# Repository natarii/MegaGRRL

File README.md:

MegaGRRL - Real Hardware Sega Genesis VGM Player
========
**MegaGRRL** is an ESP32-powered VGM player, playing tracks from the Sega Mega Drive/Genesis, Master System, and more on real YM2612 and SN76489 sound chips.

## Overview
MegaGRRL is a system comprised of ESP32-powered hardware to interface with original YM2612 and SN76489 sound chips, and FreeRTOS-based firmware using the ESP-IDF framework. Its playback engine is focused on high accuracy and supporting as many features of the VGM file format as possible. It is a completely standalone player, requiring no connection to a host PC. MegaGRRL OS has a fully-featured, easy to use UI, and several unique features which make it the premier hardware playback solution.

There are currently two main hardware versions. The same firmware targets both.
  * **MegaGRRL Desktop**
  * **MegaGRRL Portable** (still in development)

The MegaGRRL Desktop hardware also supports the following **MegaMods** allowing sound chips other than the YM2612/SN76489 to be used:
  * **OPNA MegaMod** - Uses the OPNA (YM2608). Can also play VGMs for OPN (YM2203) and AY-3-8910.
  * **OPL3 MegaMod** - Uses the OPL3 (YMF262). Can also play VGMs for OPL2 (YM3812) and OPL (YM3526).

This repository contains the MegaGRRL OS firmware, and includes the hardware as submodules. Use `--recursive` when cloning the repo to get the hardware files as well.

  * **esp-idf-patches/** - ESP-IDF v3.3.4 SPI master driver patches, required for build
  * **hardware/** - Hardware files for all base board versions, and MegaMods for the Desktop version
  * **firmware/** - Firmware for the ESP32
  * **utils/** - Utilities, such as for packing firmware updates

## Compiling and initial flash
  * Windows users: A complete guide is available [here](https://git.agiri.ninja/snippets/3).
  * Other platforms: MegaGRRL OS is built like a standard ESP-IDF v3.3.4 project, but some patches are required. Please see [doc/compiling.md](https://git.agiri.ninja/natalie/megagrrl/-/blob/master/doc/compiling.md) for more information.

## Updating firmware
To update to the latest firmware after your player is up and running, download the latest .mgu file for your hardware version (desktop or portable) from the [Releases page](https://git.agiri.ninja/natalie/megagrrl/-/releases) and copy it to the SD card. Launch the update from MegaGRRL's file browser.

## Obtaining VGM files
The defacto standard Genesis/Mega Drive VGM repository is [Project 2612](https://project2612.org/). Both .vgm and .vgz files are supported, but load times are shorter if using vgm. VGMs for other sound chips can be obtained from [VGMRips](https://vgmrips.net/packs/).

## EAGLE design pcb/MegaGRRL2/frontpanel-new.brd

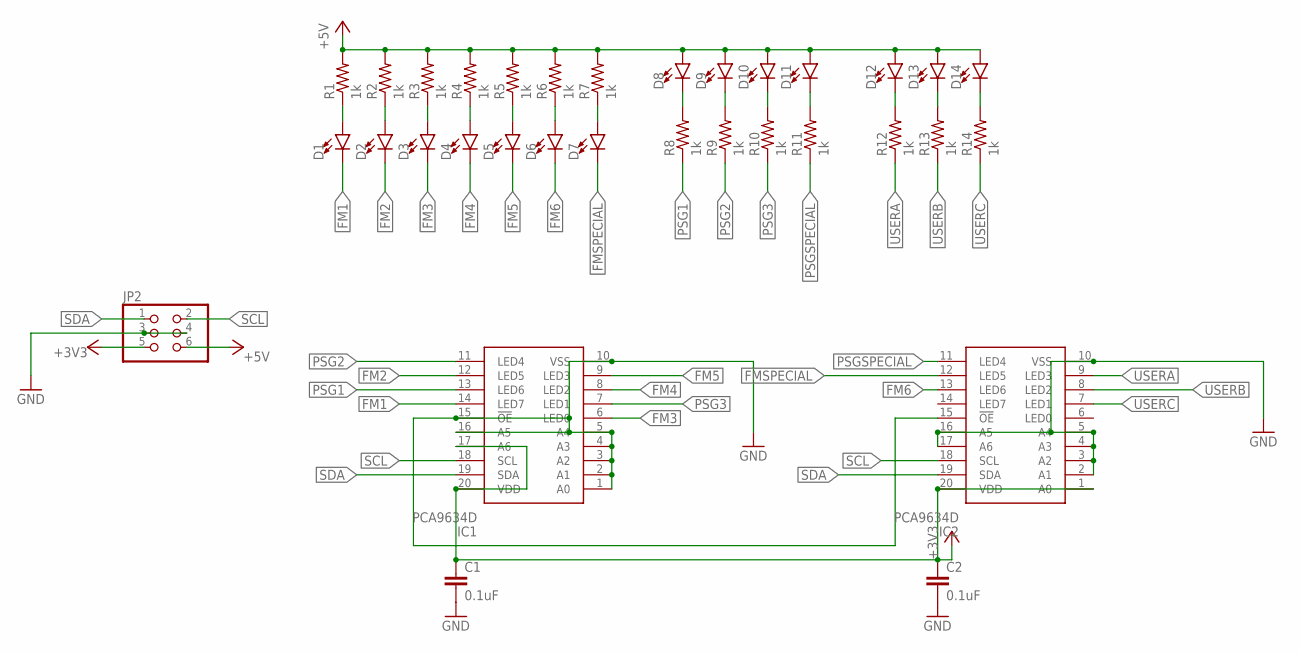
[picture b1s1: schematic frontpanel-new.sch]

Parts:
C1, C2: 0.1uF; C0805
D1, D2, D3, D4, D5, D6, D7, D8, D9, D10, D11, D12, D13, D14: AM2520; AM2520HOLE
IC1, IC2: PCA9634D; SOIC127P1032X265-20N
JP2: PINHD-2X3SMT; 2X03_SMT
R1, R2, R3, R4, R5, R6, R7, R8, R9, R10, R11, R12, R13, R14: 1k; R0805

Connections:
+3V3: C1.1, C2.1, IC1.17 (A6), IC1.20 (VDD), IC2.1 (A0), IC2.20 (VDD), JP2.5
+5V: D8.A, D9.A, D10.A, D11.A, D12.A, D13.A, D14.A, JP2.6, R1.2, R2.2, R3.2, R4.2, R5.2, R6.2, R7.2
FM1: D1.C, IC1.14 (LED7)
FM2: D2.C, IC1.12 (LED5)
FM3: D3.C, IC1.6 (LED0)
FM4: D4.C, IC1.8 (LED2)
FM5: D5.C, IC1.9 (LED3)
FM6: D6.C, IC2.13 (LED6)
FMSPECIAL: D7.C, IC2.12 (LED5)
GND: C1.2, C2.2, IC1.1 (A0), IC1.2 (A1), IC1.3 (A2), IC1.4 (A3), IC1.5 (A4), IC1.10 (VSS), IC1.15 (!OE), IC1.16 (A5), IC2.2 (A1), IC2.3 (A2), IC2.4 (A3), IC2.5 (A4), IC2.10 (VSS), IC2.15 (!OE), IC2.16 (A5), IC2.17 (A6), JP2.3, JP2.4
unnamed: D12.C, R12.2
unnamed: D1.A, R1.1
unnamed: D5.A, R5.1
unnamed: D3.A, R3.1
unnamed: D6.A, R6.1
unnamed: D4.A, R4.1
unnamed: D2.A, R2.1
unnamed: D7.A, R7.1
unnamed: D8.C, R8.2
unnamed: D9.C, R9.2
unnamed: D10.C, R10.2
unnamed: D11.C, R11.2
unnamed: D13.C, R13.2
unnamed: D14.C, R14.2
PSG1: IC1.13 (LED6), R8.1
PSG2: IC1.11 (LED4), R9.1
PSG3: IC1.7 (LED1), R10.1
PSGSPECIAL: IC2.11 (LED4), R11.1
SCL: IC1.18 (SCL), IC2.18 (SCL), JP2.2
SDA: IC1.19 (SDA), IC2.19 (SDA), JP2.1
USERA: IC2.9 (LED3), R12.1
USERB: IC2.8 (LED2), R13.1
USERC: IC2.7 (LED1), R14.1

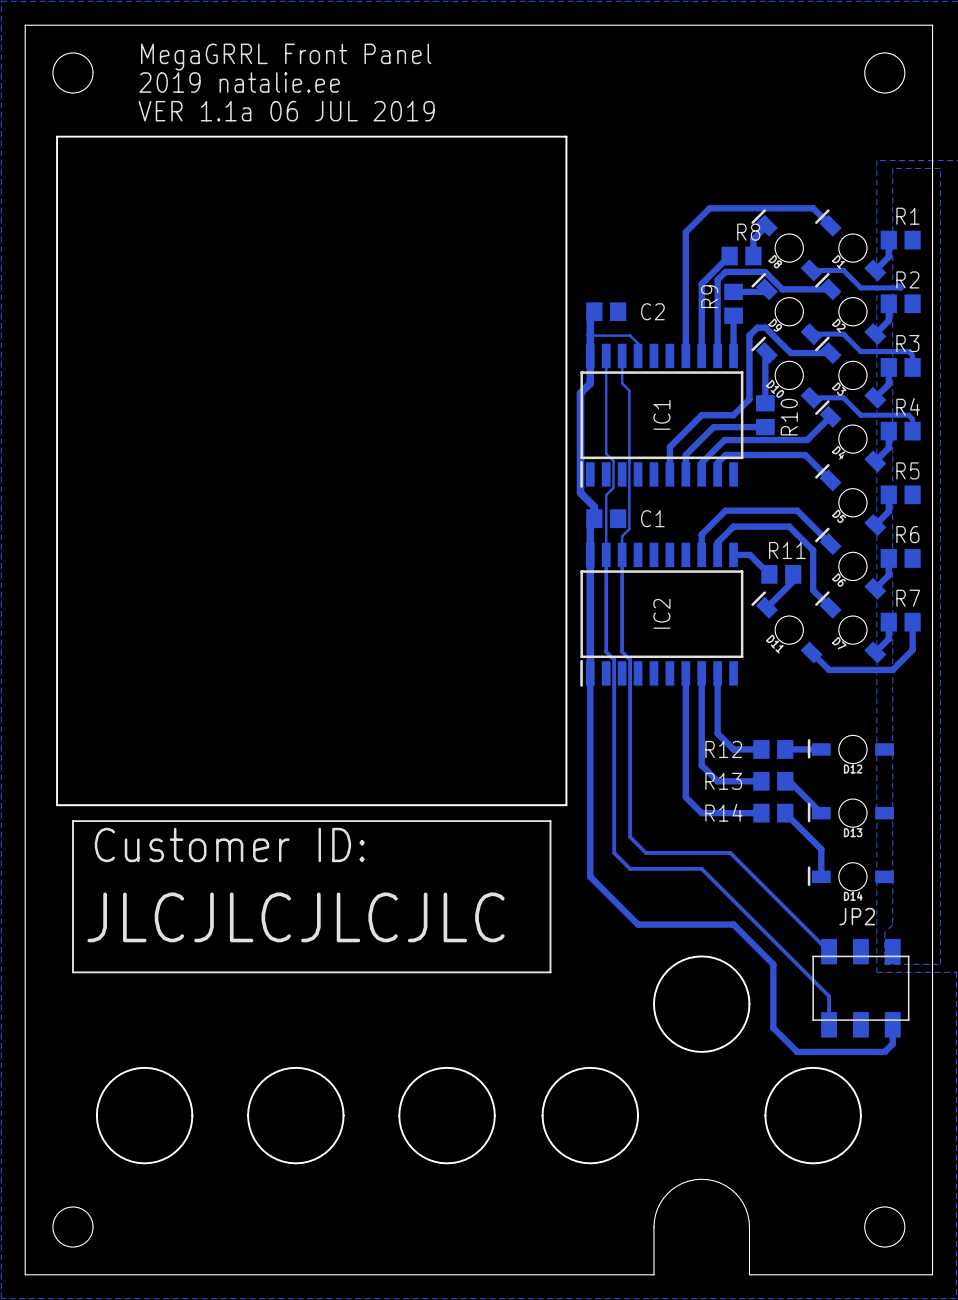
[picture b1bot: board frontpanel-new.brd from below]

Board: 2 copper layers, 72.3 x 99.6 mm, 33 parts (33 on the bottom side), 33 nets.

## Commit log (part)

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2020-03-02 add basic opm support
2020-03-13 driver: fix opna muting on opn tracks
2020-03-21 Add note about macOS/BSD serial device paths
2020-03-21 Fix options-category clamping
2020-03-22 filebrowser cleanup
2020-03-22 more filebrowser cleanup
2020-03-29 Clear paused status when stopping
    Fixes #60
2020-04-12 driver: keep track of ssg level on opn as well
2020-04-12 make softbar a little bit prettier
2020-04-12 driver: restore cpu usage tracking
2020-04-12 leddrv: don't apply brightness LUT on user leds
2020-04-13 WIP debug display
2020-04-13 bump version
2020-04-13 start moving some ui object pointers into iram
2020-04-13 crank down on most task stack sizes
2020-04-13 remove old task monitor stuff
2020-04-13 optimize filebrowser. cache entire directory, only read from card once
2020-04-13 sdkconfig: disable per-file caches
2020-04-14 improve debug ui
2020-04-15 filebrowser: fix playlist position when sorted order != disk order
2020-04-15 fix crash on options save
2020-04-21 filebrowser improvements
2020-04-24 add WIP screenshot support screenshots are saved to .mega on the sd card, screenXX.tga where XX is in hex be aware that the sequence number is not saved, so rebooting will cause existing screenshots 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
2020-04-24 move hspi init into its own file
2020-04-25 filebrowser: fix history/sorting issues
2020-04-25 filebrowser: increase filename roll speed
2020-04-26 support accents in vgm metadata
2020-04-26 allow vgz files to be overwritten with extracted versions
2020-04-26 add (disabled) spfm emulation menu item
2020-04-26 shorten loader runs
2020-04-26 mainmenu cleanup
2020-04-27 queue: remove handling of special playlist commands, for now
2020-04-27 fix #57
2020-04-27 fix nowplaying issues on broken vgms (fixes #25)
2020-04-27 turn off leds for muted fm channels (fixes #36)
2020-04-29 fix crash on playing compressed files with vgm extension
2020-04-29 remove old enclosure and pcb directories
2020-04-30 improve nowplaying somewhat
2020-05-01 filebrowser: fix names getting cut off
2020-05-01 filebrowser: fix crash going up in empty dir
2020-05-01 Avoid crash when opening nonexistent file
2020-05-01 Show N/A on softbar for nonexistent file
2020-05-02 change "options" to "settings" on nowplaying to match everything else
2020-05-08 nowplaying: fix time display during vgm firstwait period
2020-05-08 fix rewind during long vgm firstwait periods
2020-05-08 revamp options callbacks (resolves #63)
2020-05-08 further options revamp - prevent options file invalidation when adding/removing options
2020-05-08 prevent scrub bar from jumping to start of loop at track end
2020-05-12 add symbols to 10pt font
2020-05-12 improve settings ui
2020-05-13 resolve #61
2020-06-14 don't duplicate led writes, let channelmgr do all the updates
2020-06-14 channelmgr could use a little more stack
2020-06-14 additional options debugging
2020-06-14 clean up ui upon boot
2020-06-14 increase max open files
2020-06-14 add narrow font option for filebrowser
2020-06-14 boot: show checking for core in log
2020-06-14 fix missing symbols in narrow font - lvgl font converter bug?!
2020-06-16 add (very beta) pitch support
2020-06-16 fix fwupdate build
2020-06-20 fix key repeat on pitch control
2020-06-20 allow fading out at the end of looping tracks
2020-06-20 fix looping when loop count decreased during playback of later loops
2020-06-22 further debug improvements
2020-06-28 fix rare incorrect scrub bar position on nowplaying
2020-06-28 fix nowplaying screen not stopping when repeat none is set
2020-07-11 additional debug improvements
2020-08-29 Slightly more graceful handling of failed vgz extraction
2020-08-29 Disable PCM LED when PCM is muted
2020-08-30 Display version number on home screen
2020-09-03 Improve behavior of pitch controls
2020-09-07 Fix User LED regression
2020-09-13 Fix total loop count display
2020-10-03 Improve firmware flashing UX/reliability
2020-10-03 Support single AY-3-8910 playback on OPNA
2020-10-03 Add debugging to catch invalid FM reg writes
2020-10-03 Fix clock calculations for disabled chips
2020-10-05 Optimize DacStreams, reduce number of redundant file reads
2020-10-06 FileBrowser: ignore recycle bin
2020-10-09 Split options into types and subtypes
2020-10-09 Fix fade length option
2020-10-09 More performant handling of large playlists
2020-10-09 Driver: Clean up OPNA timing stuff
2020-10-09 Clean up fadeouts, add OPNA support
2020-10-11 Add CRC and backup/recovery to options file
2020-10-11 Add long label handling option
2020-10-11 Hide OPNA upload accel option if no OPNA present
2020-10-14 Basic shuffle support
2020-10-14 Improve shuffle UX
2020-10-14 Add shuffle icon to statusbar
2020-10-14 Statusbar: Fix extract icon position when shuffle enabled. Really should clean up this mess...
2020-10-14 Fix shuffle behavior, optimize queue
2020-10-15 Stick skipped filenames into flash
2020-10-15 Add full SD card shuffling
2020-10-15 Fix options screen back button
2020-10-22 Make brightness option work for now, until the LUT stuff is done
2020-10-24 New APLL-based high precision FM clock output
2020-10-25 Add megapacker.pl script to create .mgu updater files
    This is a relatively simple Perl script that takes app and/or updater
    ESP32 .bin image(s) and packs them into the .mgu format that is expected
    by the MegaGRRL firmware when initiating firmware updates from the File
    Browser.
    Example usage, for an app-only update on the (d)esktop version:
    perl utils/megapacker.pl --app=firmware/build/megagrrl.bin --hw=d --outfile=megagrrl.mgu
2020-10-25 Don't truncate app_elf_sha256 when parsing esp_app_desc_t
    This isn't currently used except to output debug-esque information about
    the parsed header.
2020-10-31 Move a few more things into IRAM
2020-11-01 Add pitch reset button to nowplaying
2020-11-01 Fix #69
2020-11-01 Don't save options file if we shuffle all, and shuffle was already enabled
2020-11-01 Add local buffer to dacstream find task
2020-11-05 Preliminary fade support for OPNA ADPCM/rhythm
2020-11-05 Small optimization: Don't write to YM2612 DAC during first wait period
2020-12-06 Remove debug output from driver
2020-12-06 Fix VGMs with very short looping periods failing to begin playback
2020-12-06 Don't let elapsed time exceed total during fadeouts
2020-12-07 Ignore AY-3-8910 stereo masks
2020-12-17 Implement modal window
2020-12-23 Optimize queue handling
2020-12-23 Add easter egg!
2021-01-09 Fix channel muting regression
2021-01-09 Disable unnecessary debug
2021-02-08 Revert specifically bus dedup for now.
2021-02-26 Warn when playing known bad VGMs
2021-02-26 Fix missing scroll type text
2021-02-27 Use filename like megagrrl_<hwver>_<type>_<version>.mgu if --outfile is unset
    Example filenames:
    - megagrrl_d_app_v0.98dev-test.mgu
    - megagrrl_d_app+updater_v0.98dev-test.mgu
    - megagrrl_d_updater_v0.97dev-103-gbbbc2dd-dirty.mgu
2021-02-28 Improve dacstream fast forward behavior
2021-02-28 Improve key debounce
2021-02-28 Further improve debounce
2021-02-28 Ignore bit 31 of OPN2 clock
2021-03-07 Improve channel LED key-on behavior
2021-03-07 Improve VGM timing accuracy
2021-03-07 Get rid of special trim handling
2021-03-07 Fix DAC LED flash at start of track
2021-03-07 Revert "Fix DAC LED flash at start of track"
    This reverts commit 458d77ae40074998f4beb8615c595b64717e3bc7.
2021-03-07 Only do all of this on OPN2/PSG hardware
2021-03-07 Same for slip
2021-03-07 Fix occasional missing FM1
2021-03-14 Some VGMs have very broken gd3 offsets, let's not break on that
2021-03-18 Update known bad VGM list
2021-03-20 Revert "Force OPN2 test registers to first bank"
    This reverts commit 109b5acb3bae3d9575ef16c8181dd12c87442acd.
2021-03-20 Revert "Revert "Force OPN2 test registers to first bank""
    This reverts commit d48cdcef76bfcdc47f41b436ac844699155e7bfe.
2021-03-20 Just let writes to registers in wrong bank fall through
2021-04-17 Fix erroneously applying bad vgm handling to all vgms
2021-04-17 Catch some SD card errors and try to recover gracefully
2021-04-17 Add loading spinner to file browser
2021-04-17 Scope cleanup
2021-04-17 Display a warning when VGZ extraction fails
2021-04-17 Clear nowplaying display when VGZ extraction fails
2021-04-17 Catch SD errors in Player
2021-04-17 Missing include for queue status in loader
2021-04-17 Prevent task priority issues from stopping Loader upon SD error
2021-04-17 Quick fix to allow OPNA playback on OPN2 with correct clock
2021-04-17 Graceful handling of directories larger than cache area
2021-04-19 lcddma: Remove unnecessary debug
2021-04-19 Implement runtime log level options
2021-04-19 Improve loading spinner on file browser
2021-04-19 Initial progress on tutorial
2021-04-19 Fix nowplaying tutorial
2021-04-25 Clean up driver debug
2021-04-25 Revamp LED brightness
2021-04-30 Repo reorganization
2021-05-18 LedDrv: Allow forcing LED brightness to 0
2021-05-18 Fix erroneous loglevel change at boot
2021-05-18 Show loading spinner when going back in filebrowser
2021-05-18 Remove confusing "truncate" scroll type
2021-07-09 Increase stack for BatteryMgr task
2021-07-09 Fix loop count display when nothing playing
2021-07-09 Invalidate shuffle cache upon SD card swap
2021-07-12 Fix support for first SN76489 in dual-chip vgms
2021-07-12 Fix #78
2021-07-13 Prevent reading invalid clocks on pre-1.51 VGMs with OPNA hardware
2021-07-13 Mask off 3438 bit when reading OPN2 clock with OPNA hardware
2021-07-14 Player: Fix dual chip bit detection in some cases
2021-11-01 Improve supported chip detection
2021-11-06 Fix #90 - invalid clock check on OPLL+DCSG MegaMod
2021-11-06 Use non-reversed data bus for DCSG on Denjhang's OPLL+DCSG mod
2021-11-06 Rename PSG->DCSG
2022-01-31 Correct DCSG frequency latch handling - fixes #106
2023-01-01 Add basic support for alternate LCD types
2023-01-01 Improve alternate DCSG type support
2023-01-01 Preliminary improvements to unsupported chip handling
2023-01-01 Refactor handling of the bad VGM flags
2023-01-01 HAL LCD selection should default to standard ILI9341
2023-01-02 Fix loading VGMs that don't zerofill the entire possible header area
2023-01-14 Add vgm spec to doc
2023-01-18 refactor
2023-03-31 Refactor port -> addr
2023-05-27 Use better algorithm to determine APLL parameters
2023-05-28 Player: Add proper handling of gzip flags
2023-10-31 Basic OPN+OPLL MegaMod support
2023-11-03 Ignore SCC writes
2023-11-04 Driver: restore early resets
2023-11-19 2xOPN support
2023-11-24 2xpsg wip
2023-11-25 Fix PSG signal transition order. Closes #125
2023-11-25 Fix OPN+OPLL MegaMod OPLL writes falling through to ignore handler
2023-12-02 Use correct chip select for OPLL+DCSG mod
2024-02-26 Add 2xSAA1099 support
2024-04-09 Relicense to GPLv3 Contributors have been contacted and agreed to this relicensing.
2024-07-09 Vgm: Graceful VGM data offset handling for some spec-violating files
2024-08-20 UserLed: Fix incorrect LEDs under certain combinations of settings
2024-09-15 Queue: Random API has changed
2024-09-15 I2C: API changes
2024-09-15 Fwupdate: New header for mmap funcs
2024-09-15 Ioexp: GPIO API change
2024-09-15 Mainmenu: Fix return type issue
2024-09-16 LVGL cmake build
2024-09-16 Fix extrafonts lvgl include
2024-09-16 cmake-ize megastream
2024-09-16 cmake work
2024-09-23 Fix sdcard
2024-09-23 sdkconfig: re-disable task wdt on cpu1
2024-09-23 Clk: Fixes for 5.x
2024-09-23 idf component manifest
2024-09-25 Bump version so idf5x testing is obvious
2024-09-25 Disable some stuff in sdkconfig
2024-09-25 Revert "Disable some stuff in sdkconfig"
    This reverts commit 58092dd0a58db66545c1c307f1322906d8c1a555.
2024-09-25 Optimize for perf
2025-02-14 Player: Don't reopen file upon restarting currently playing track
2025-03-31 Support showing FM/DCSG writes on user LEDs
2025-06-11 idf_component: Set minimum version 5.4.1
2025-06-11 Vendor miniz
2025-06-11 Muting: Invert toggle-all behavior
2025-06-11 Driver: SPI write bench
2025-06-11 bump ver
2025-06-13 Driver: Tweak OPN2 write delays
2025-06-13 UserLed: Slight improvement to chip write LED behavior
2025-06-16 Migrate to ESP-IDF 5.4.1

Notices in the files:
parts and their libraries:
kingbright-am2520: Licensing: Creative Commons ShareAlike 4.0 International - https://creativecommons.org/licenses/by-sa/4.0
